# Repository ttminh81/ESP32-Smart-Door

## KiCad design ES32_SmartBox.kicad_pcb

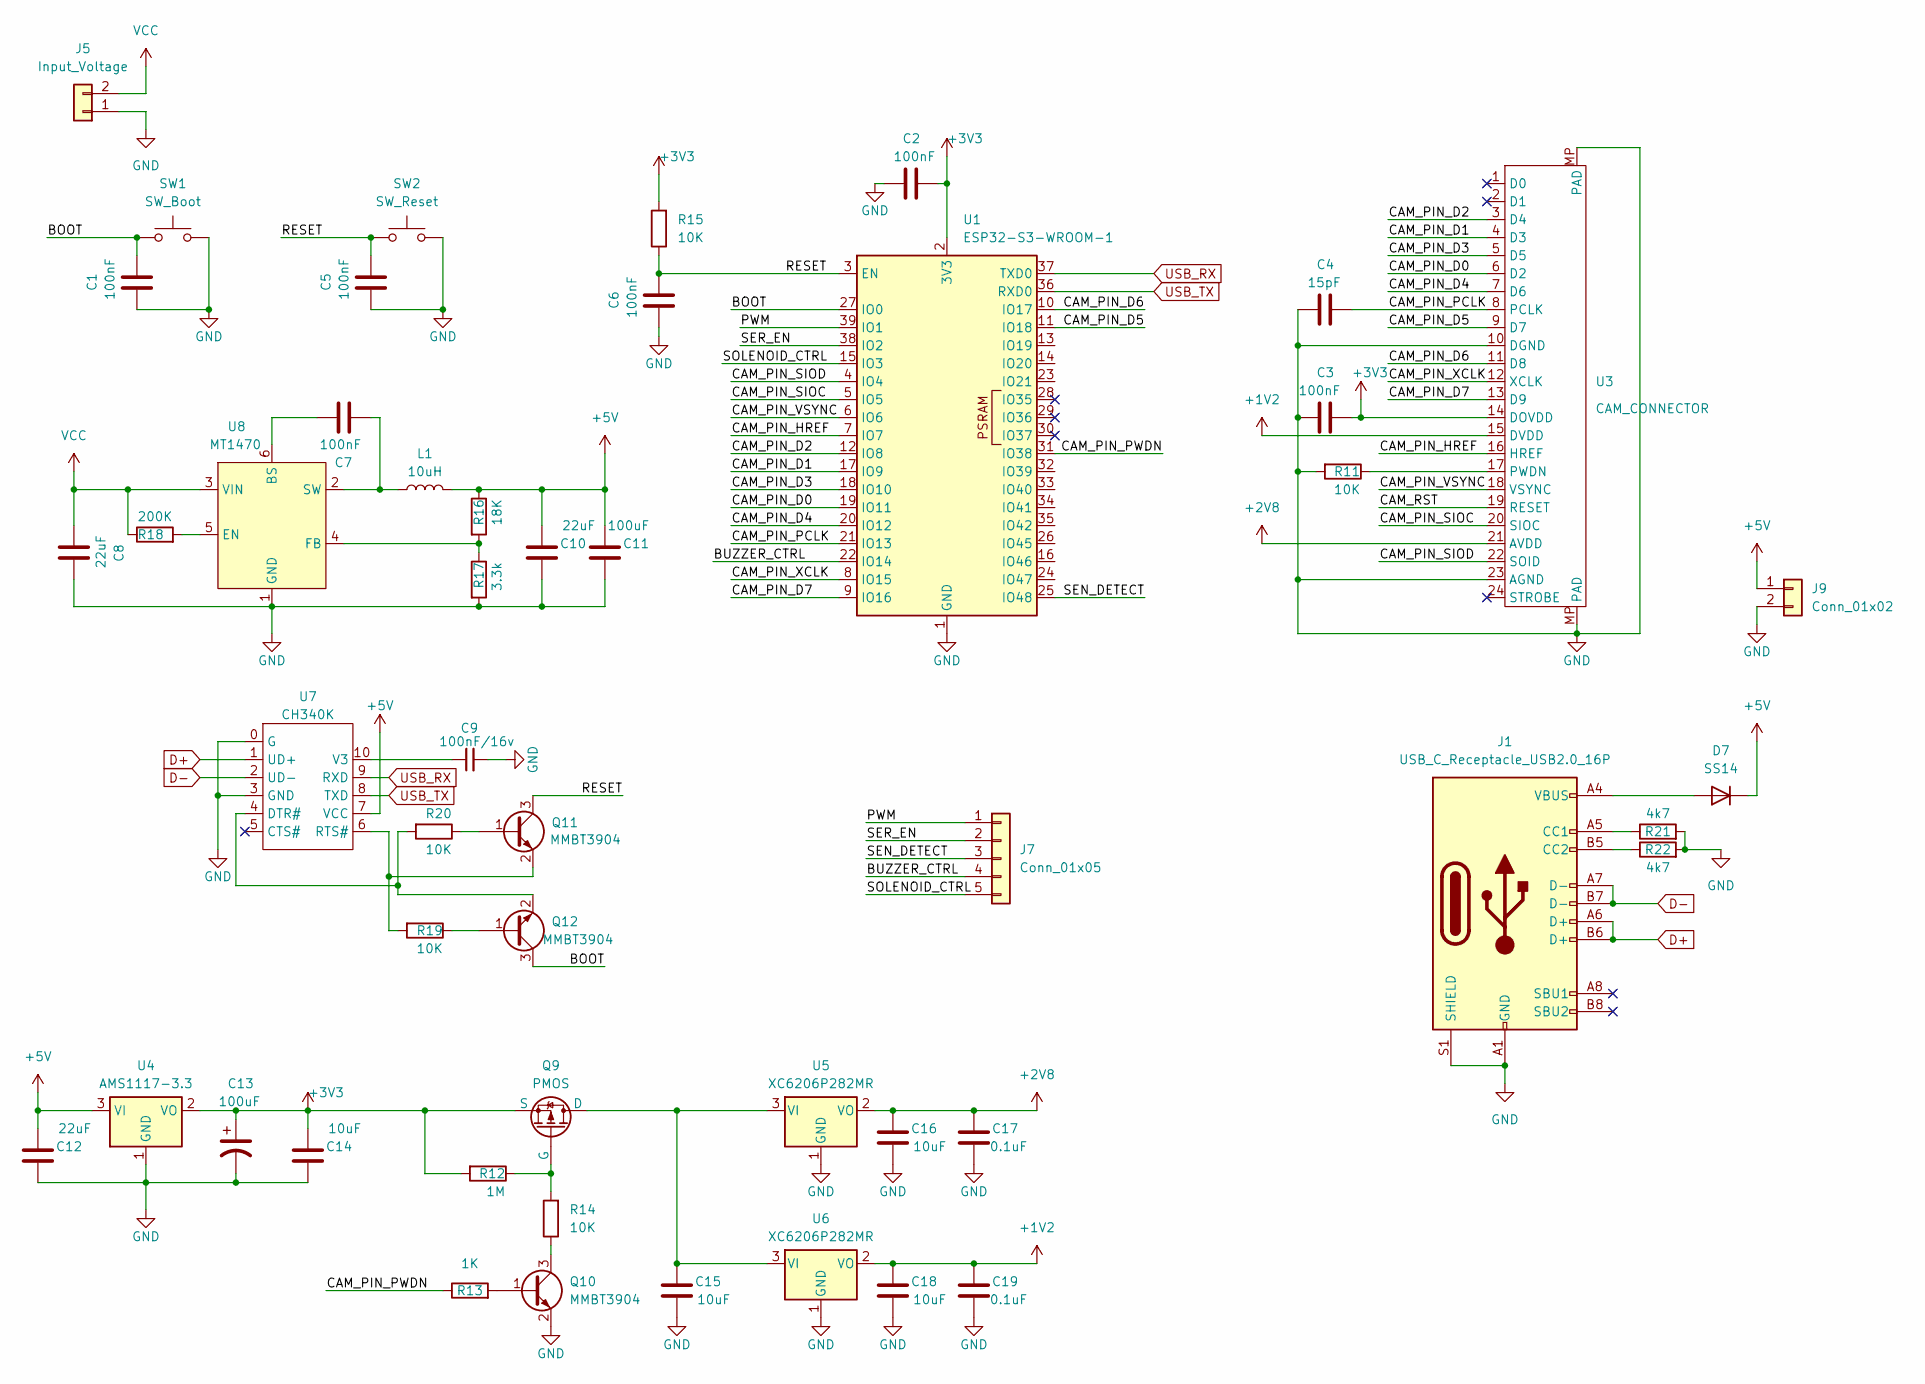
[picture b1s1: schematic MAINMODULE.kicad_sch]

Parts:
C1, C2, C3, C5, C6, C7: 100nF; C_0603_1608Metric
C4: 15pF; C_0603_1608Metric
C8, C10, C12: 22uF; C_0805_2012Metric
C9: 100nF/16v; C_0603_1608Metric
C11, C13: 100uF; C_1210_3225Metric
C14, C15, C16, C18: 10uF; C_0805_2012Metric
C17, C19: 0.1uF; C_0603_1608Metric
D7: SS14; D_SMA
J1: USB_C_Receptacle_USB2.0_16P; USB_C_Receptacle_G-Switch_GT-USB-7010ASV
J5: Input_Voltage; TerminalBlock_Phoenix_MKDS-1,5-2-5.08_1x02_P5.08mm_Horizont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
J7: Conn_01x05; PinHeader_1x05_P2.54mm_Vertical
J9: Conn_01x02; Molex_KK-254_AE-6410-02A_1x02_P2.54mm_Vertical
L1: 10uH; 0603_R100
Q9: PMOS; SOT-23
Q10, Q11, Q12: MMBT3904; SOT-23
R11, R14, R15, R19, R20: 10K; R_0603_1608Metric
R12: 1M; R_0603_1608Metric
R13: 1K; R_0603_1608Metric
R16: 18K; R_0603_1608Metric
R17: 3.3k; R_0603_1608Metric
R18: 200K; R_0603_1608Metric
R21, R22: 4k7; R_0603_1608Metric
SW1: SW_Boot; SW_Push_SPST_NO_Alps_SKRK
SW2: SW_Reset; SW_Push_SPST_NO_Alps_SKRK
U1: ESP32-S3-WROOM-1
U3: CAM_CONNECTOR; TE_2-1734839-4_1x24-1MP_P0.5mm_Horizontal
U4: AMS1117-3.3; SOT-223-3_TabPin2
U5, U6: XC6206P282MR; SOT-23-3
U7: CH340K; SSOP-10_3.9x4.9mm_P1.00mm
U8: MT1470; SOT-23-6

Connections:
+1V2: C18.2, C19.2, U3.15 (DVDD), U6.2 (VO)
+2V8: C16.2, C17.2, U3.21 (AVDD), U5.2 (VO)
+3V3: C2.1, C3.1, C13.1, C14.2, Q9.3 (S), R12.2, R15.2, U1.2 (3V3), U3.14 (DOVDD), U4.2 (VO)
+5V: C10.2, C11.2, C12.2, D7.1 (K), J9.1, L1.2, R16.1, U4.3 (VI), U7.7 (VCC); also elsewhere on the board
/MAIN MODULE/BOOT: C1.1, Q12.3 (C), SW1.1, U1.27 (IO0)
/MAIN MODULE/BUZZER_CTRL: J7.4, U1.22 (IO14)
/MAIN MODULE/CAM_PIN_D0: U1.19 (IO11), U3.6 (D2)
/MAIN MODULE/CAM_PIN_D1: U1.17 (IO9), U3.4 (D3)
/MAIN MODULE/CAM_PIN_D2: U1.12 (IO8), U3.3 (D4)
/MAIN MODULE/CAM_PIN_D3: U1.18 (IO10), U3.5 (D5)
/MAIN MODULE/CAM_PIN_D4: U1.20 (IO12), U3.7 (D6)
/MAIN MODULE/CAM_PIN_D5: U1.11 (IO18), U3.9 (D7)
/MAIN MODULE/CAM_PIN_D6: U1.10 (IO17), U3.11 (D8)
/MAIN MODULE/CAM_PIN_D7: U1.9 (IO16), U3.13 (D9)
/MAIN MODULE/CAM_PIN_HREF: U1.7 (IO7), U3.16 (HREF)
/MAIN MODULE/CAM_PIN_PCLK: C4.1, U1.21 (IO13), U3.8 (PCLK)
/MAIN MODULE/CAM_PIN_PWDN: R13.1, U1.31 (IO38)
/MAIN MODULE/CAM_PIN_SIOC: U1.5 (IO5), U3.20 (SIOC)
/MAIN MODULE/CAM_PIN_SIOD: U1.4 (IO4), U3.22 (SOID)
/MAIN MODULE/CAM_PIN_VSYNC: U1.6 (IO6), U3.18 (VSYNC)
/MAIN MODULE/CAM_PIN_XCLK: U1.8 (IO15), U3.12 (XCLK)
/MAIN MODULE/CAM_RST: U3.19 (RESET)
/MAIN MODULE/PWM: J7.1, U1.39 (IO1)
/MAIN MODULE/RESET: C5.1, C6.1, Q11.3 (C), R15.1, SW2.1, U1.3 (EN)
/MAIN MODULE/SEN_DETECT: J7.3, U1.25 (IO48)
/MAIN MODULE/SER_EN: J7.2, U1.38 (IO2)
/MAIN MODULE/SOLENOID_CTRL: J7.5, U1.15 (IO3)
D+: J1.A6 (D+), J1.B6 (D+), U7.1 (UD+)
D-: J1.A7 (D-), J1.B7 (D-), U7.2 (UD-)
GND: C1.2, C2.2, C3.2, C4.2, C5.2, C6.2, C8.1, C9.2, C10.1, C11.1, C12.1, C13.2, C14.1, C15.1, C16.1, C17.1, C18.1, C19.1, J1.A1 (GND), J1.A12 (GND), J1.B1 (GND), J1.B12 (GND), J1.S1 (SHIELD), J5.1, J9.2, Q10.2 (E), R11.2, R17.2, R21.2, R22.2, SW1.2, SW2.2, U1.1 (GND), U1.40 (GND), U1.41 (GND), U3.10 (DGND), U3.23 (AGND), U3.MP (PAD), U4.1 (GND), U5.1 (GND), U6.1 (GND), U7.0 (G), U7.3 (GND), U8.1 (GND); also elsewhere on the board
unnamed: D7.2 (A), J1.A4 (VBUS), J1.A9 (VBUS), J1.B4 (VBUS), J1.B9 (VBUS)
unnamed: J1.A5 (CC1), R21.1
unnamed: J1.B5 (CC2), R22.1
unnamed: C15.2, Q9.1 (D), U5.3 (VI), U6.3 (VI)
unnamed: Q9.2 (G), R12.1, R14.2
unnamed: Q10.1 (B), R13.2
unnamed: Q10.3 (C), R14.1
unnamed: Q11.1 (B), R20.1
unnamed: Q11.2 (E), R19.2, U7.6 (RTS#)
unnamed: Q12.1 (B), R19.1
unnamed: Q12.2 (E), R20.2, U7.4 (DTR#)
unnamed: R11.1, U3.17 (PWDN)
unnamed: C9.1, U7.10 (V3)
unnamed: C7.1, U8.6 (BS)
unnamed: R18.2, U8.5 (EN)
unnamed: R16.2, R17.1, U8.4 (FB)
unnamed: C7.2, L1.1, U8.2 (SW)
USB_RX: U1.37 (TXD0), U7.9 (RXD)
USB_TX: U1.36 (RXD0), U7.8 (TXD)
VCC: C8.2, J5.2, R18.1, U8.3 (VIN); also elsewhere on the board

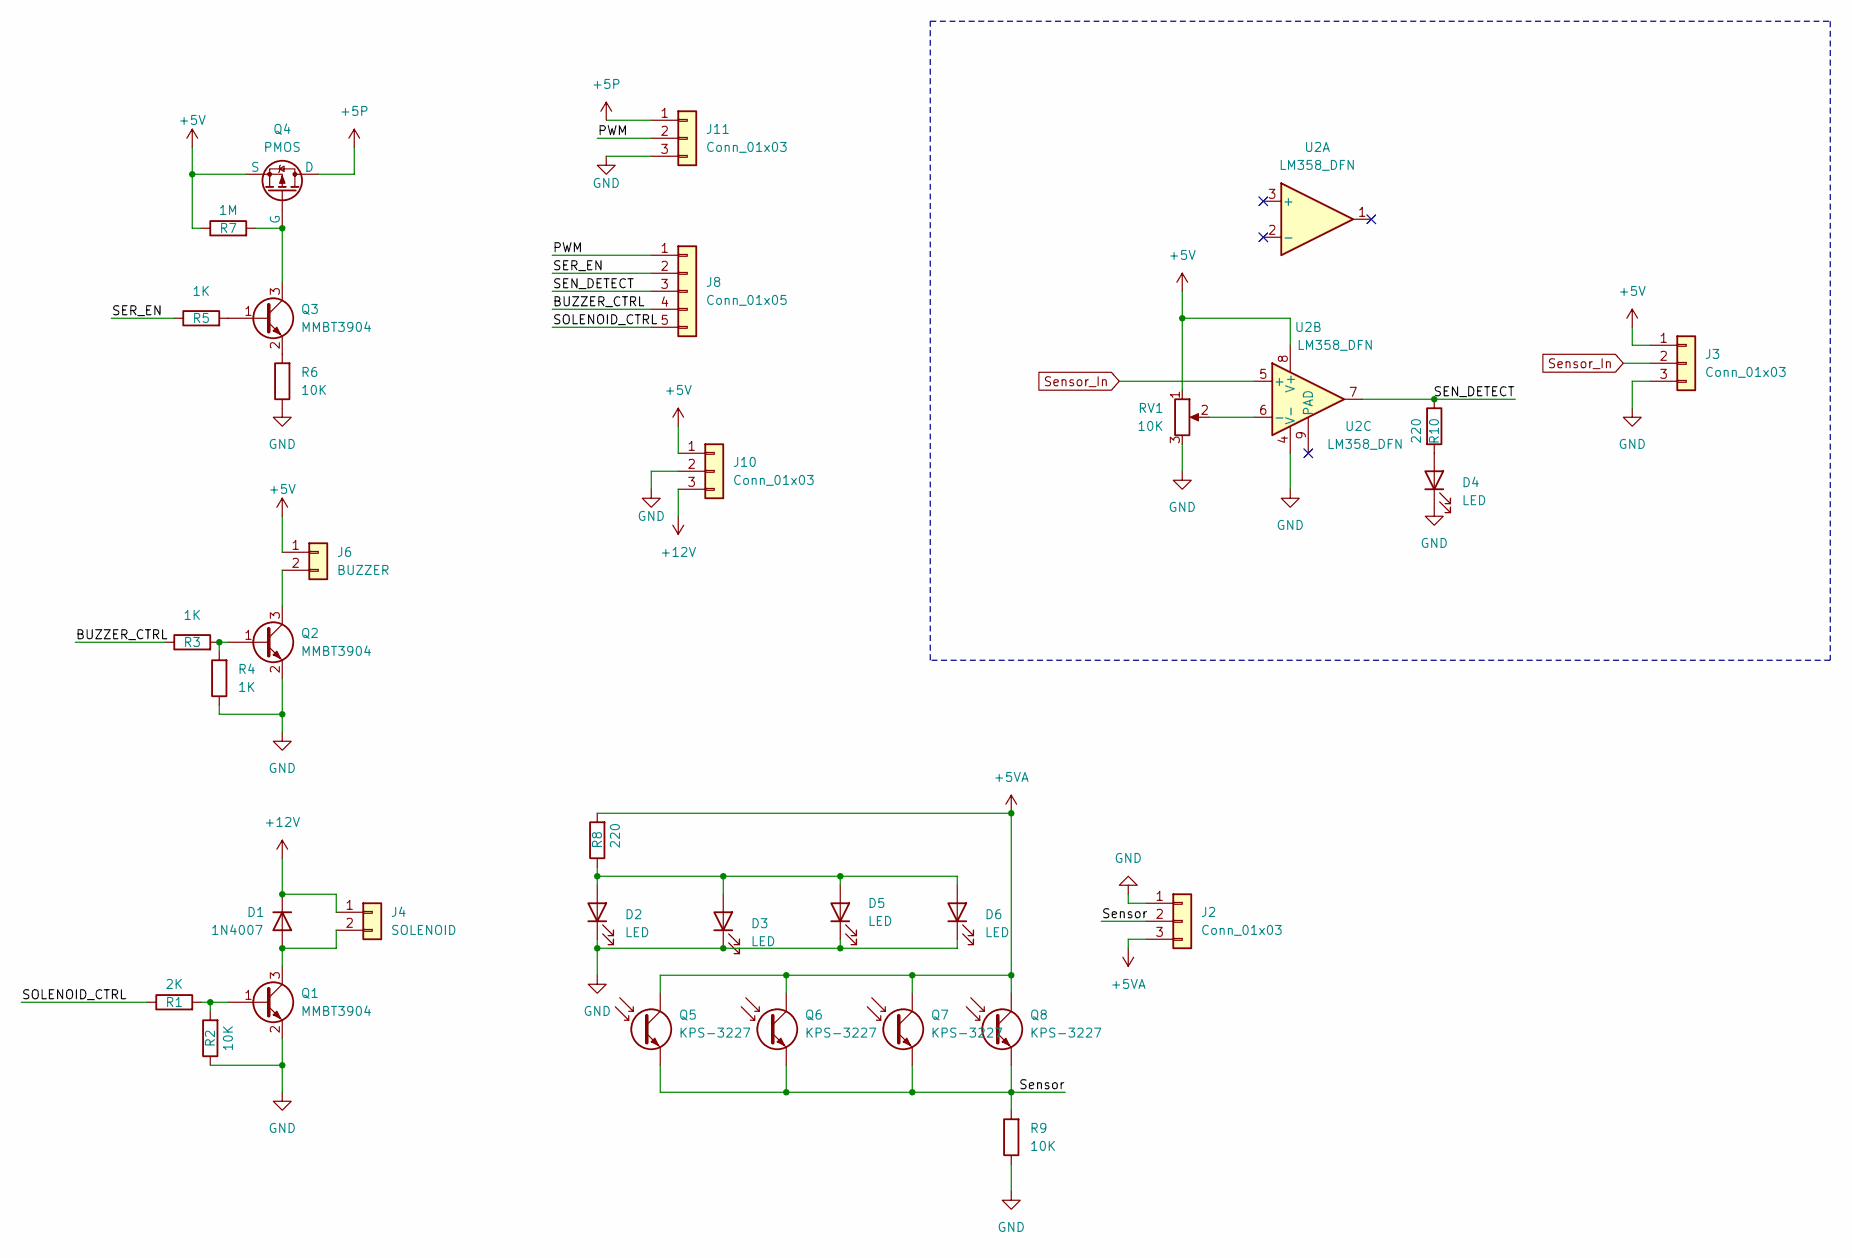
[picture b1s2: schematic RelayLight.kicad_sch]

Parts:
D1: 1N4007; D_DO-41_SOD81_P10.16mm_Horizontal
D2, D3, D5, D6: LED; LED_1206_3216Metric
D4: LED; LED_0603_1608Metric
J2, J3: Conn_01x03; JST_XH_S3B-XH-A-1_1x03_P2.50mm_Horizontal
J4: SOLENOID; Molex_KK-254_AE-6410-02A_1x02_P2.54mm_Vertical
J6: BUZZER; Molex_KK-254_AE-6410-02A_1x02_P2.54mm_Vertical
J8: Conn_01x05; PinHeader_1x05_P2.54mm_Vertical
J10, J11: Conn_01x03; Molex_KK-254_AE-6410-03A_1x03_P2.54mm_Vertical
Q1, Q2, Q3: MMBT3904; SOT-23
Q4: PMOS; SOT-23
Q5, Q6, Q7, Q8: KPS-3227; LED_1206_3216Metric
R1: 2K; R_0603_1608Metric
R2, R6, R9: 10K; R_0603_1608Metric
R3, R4, R5: 1K; R_0603_1608Metric
R7: 1M; R_0603_1608Metric
R8, R10: 220; R_0603_1608Metric
RV1: 10K; Potentiometer_Piher_PT-6-V_Vertical
U2: LM358_DFN; SOIC-8-1EP_3.9x4.9mm_P1.27mm_EP2.29x3mm

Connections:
+5P: J11.1, Q4.1 (D)
+5V: J3.1, J6.1, J10.1, Q4.3 (S), R7.1, RV1.1, U2.8 (V+); also elsewhere on the board
+5VA: J2.3, Q5.1, Q5.3, Q6.1, Q6.3, Q7.1, Q7.3, Q8.1, Q8.3, R8.2
+12V: D1.1 (K), J4.1, J10.3
/Relay + Light/BUZZER_CTRL: J8.4, R3.1
/Relay + Light/PWM: J8.1, J11.2
/Relay + Light/SEN_DETECT: J8.3, R10.1, U2.7
/Relay + Light/SER_EN: J8.2, R5.1
/Relay + Light/SOLENOID_CTRL: J8.5, R1.1
/Relay + Light/Sensor: J2.2, Q5.2, Q5.4, Q6.2, Q6.4, Q7.2, Q7.4, Q8.2, Q8.4, R9.2
GND: D2.1 (K), D3.1 (K), D4.1 (K), D5.1 (K), D6.1 (K), J2.1, J3.3, J10.2, J11.3, Q1.2 (E), Q2.2 (E), R2.1, R4.1, R6.1, R9.1, RV1.3, U2.4 (V-); also elsewhere on the board
unnamed: D1.2 (A), J4.2, Q1.3 (C)
unnamed: D2.2 (A), D3.2 (A), D5.2 (A), D6.2 (A), R8.1
unnamed: D4.2 (A), R10.2
unnamed: J6.2, Q2.3 (C)
unnamed: Q1.1 (B), R1.2, R2.2
unnamed: Q2.1 (B), R3.2, R4.2
unnamed: Q3.1 (B), R5.2
unnamed: Q3.3 (C), Q4.2 (G), R7.2
unnamed: Q3.2 (E), R6.2
unnamed: RV1.2, U2.6 (-)
Sensor_In: J3.2, U2.5 (+)

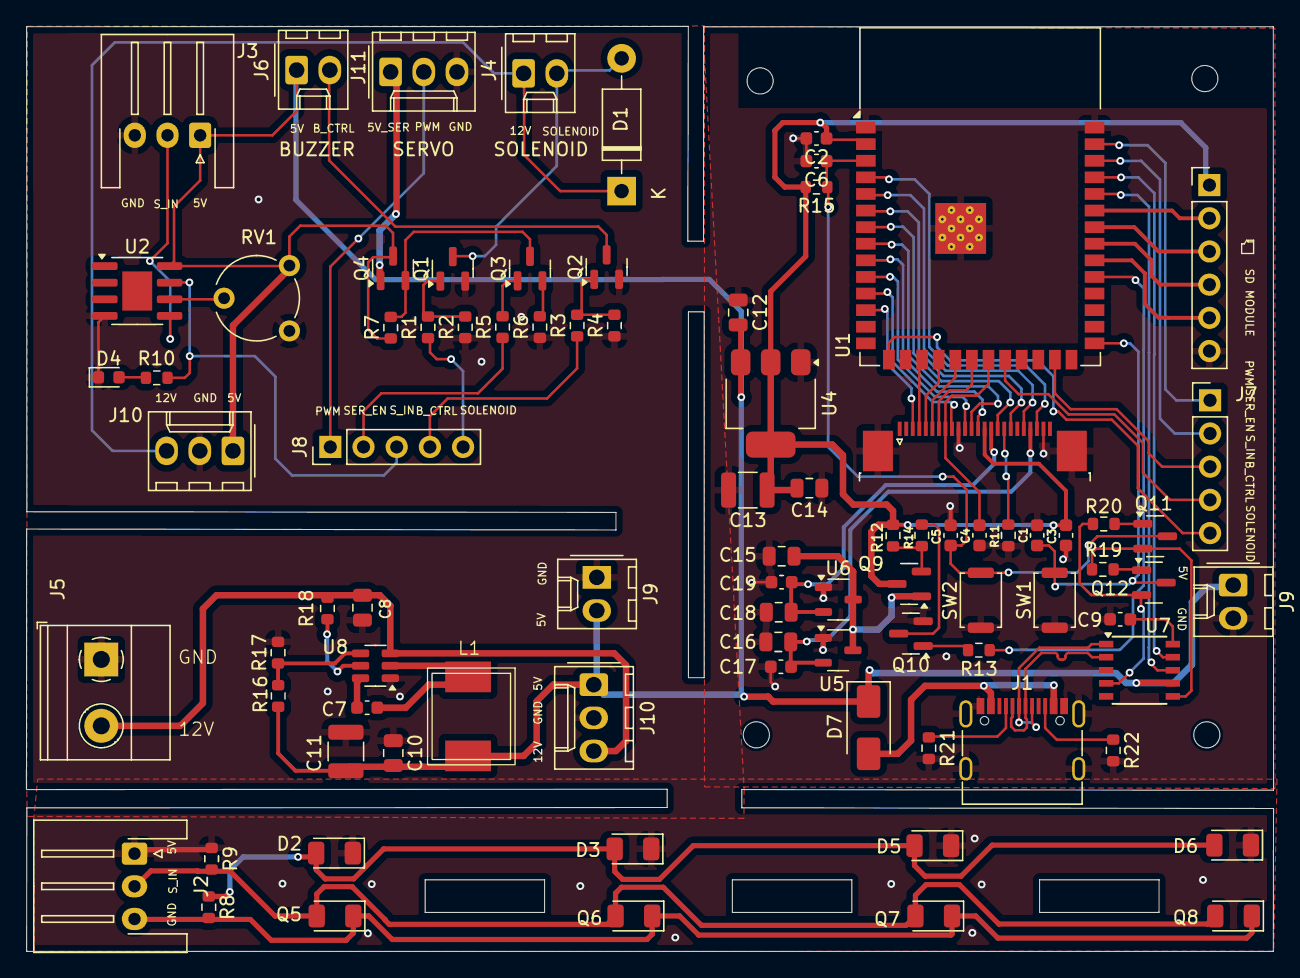
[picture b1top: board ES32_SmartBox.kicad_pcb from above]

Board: 2 copper layers, 95.4 x 70.8 mm, 85 parts (0 on the bottom side), 69 nets.

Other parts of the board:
J9#2: Conn_01x02; Molex_KK-254_AE-6410-02A_1x02_P2.54mm_Vertical
J10#2: Conn_01x03; Molex_KK-254_AE-6410-03A_1x03_P2.54mm_Vertical

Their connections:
+5V: J9#2.2, J10#2.1; also elsewhere on the board
GND: J9#2.1, J10#2.2; also elsewhere on the board
VCC: J10#2.3; also elsewhere on the board
